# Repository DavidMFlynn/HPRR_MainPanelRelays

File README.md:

# HPRR_MainPanelRelays
 Block Power Relays

Aux Relays:
2x 4PDT relays with diodes and connectors.

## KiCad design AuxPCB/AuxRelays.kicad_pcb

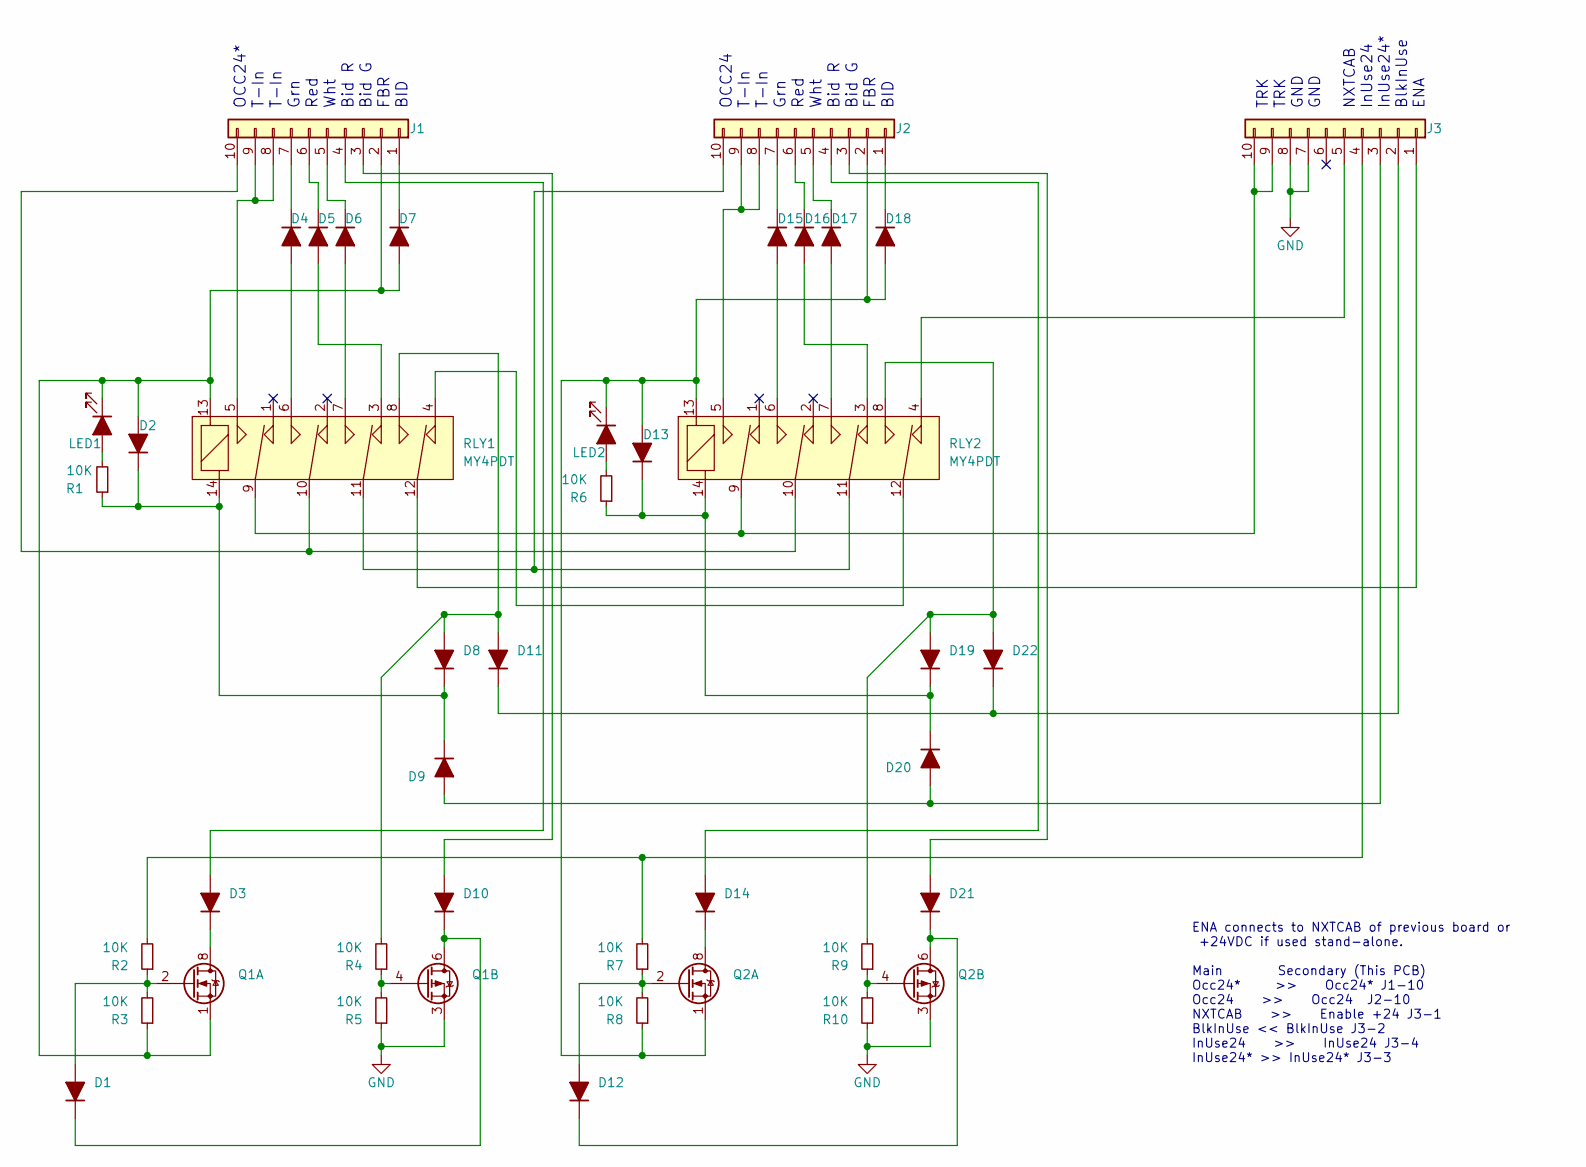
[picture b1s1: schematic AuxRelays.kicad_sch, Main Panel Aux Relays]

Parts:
D1, D2, D3, D4, D5, D6, D7, D8, D9, D10, D11, D12, D13, D14, D15, D16, D17, D18, D19, D20, D21, D22: SMA; D_SMA
J1, J2, J3: Conn_01x10; TerminalBlock_Phoenix_PT-1,5-10-3.5-H_1x10_P3.50mm_Horizont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
LED1, LED2: LED; LED_1206_3216Metric_Pad1.42x1.75mm_HandSolder
Q1, Q2: IRF7343PBF; SOIC-8_3.9x4.9mm_P1.27mm
R1, R2, R3, R4, R5, R6, R7, R8, R9, R10: 10K; R_0805_2012Metric_Pad1.20x1.40mm_HandSolder
RLY1, RLY2: MY4PDT

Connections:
GND: J3.7, J3.8, Q1.3 (1), Q2.3 (1), R5.1, R10.1
unnamed: D1.1 (K), D10.1 (K), Q1.5 (D), Q1.6 (D)
unnamed: D1.2 (A), Q1.2 (G), R2.1, R3.2
unnamed: D2.1 (K), D8.1 (K), D9.1 (K), R1.1, RLY1.14
unnamed: D2.2 (A), D7.2 (A), J1.2, LED1.1 (K), Q1.1 (S), R3.1, RLY1.13
unnamed: D3.1 (K), Q1.7 (D), Q1.8 (D)
unnamed: D3.2 (A), J1.4
unnamed: D4.1 (K), J1.7
unnamed: D4.2 (A), RLY1.6
unnamed: D5.1 (K), J1.6
unnamed: D5.2 (A), RLY1.3
unnamed: D6.1 (K), J1.5
unnamed: D6.2 (A), RLY1.7
unnamed: D7.1 (K), J1.1
unnamed: D10.2 (A), J1.3
unnamed: D11.1 (K), D22.1 (K), J3.2
unnamed: D8.2 (A), D11.2 (A), R4.2, RLY1.8
unnamed: D12.1 (K), D21.1 (K), Q2.5 (D), Q2.6 (D)
unnamed: D12.2 (A), Q2.2 (G), R7.1, R8.2
unnamed: D13.1 (K), D19.1 (K), D20.1 (K), R6.1, RLY2.14
unnamed: D13.2 (A), D18.2 (A), J2.2, LED2.1 (K), Q2.1 (S), R8.1, RLY2.13
unnamed: D14.1 (K), Q2.7 (D), Q2.8 (D)
unnamed: D14.2 (A), J2.4
unnamed: D15.1 (K), J2.7
unnamed: D15.2 (A), RLY2.6
unnamed: D16.1 (K), J2.6
unnamed: D16.2 (A), RLY2.3
unnamed: D17.1 (K), J2.5
unnamed: D17.2 (A), RLY2.7
unnamed: D18.1 (K), J2.1
unnamed: D19.2 (A), D22.2 (A), R9.2, RLY2.8
unnamed: D9.2 (A), D20.2 (A), J3.3
unnamed: D21.2 (A), J2.3
unnamed: J1.8, J1.9, RLY1.5
unnamed: J1.10, RLY1.10, RLY2.10
unnamed: J2.8, J2.9, RLY2.5
unnamed: J2.10, RLY1.11, RLY2.11
unnamed: J3.1, RLY1.12
unnamed: J3.4, R2.2, R7.2
unnamed: J3.5, RLY2.4
unnamed: J3.9, J3.10, RLY1.9, RLY2.9
unnamed: LED1.2 (A), R1.2
unnamed: LED2.2 (A), R6.2
unnamed: Q1.4 (G), R4.1, R5.2
unnamed: Q2.4 (G), R9.1, R10.2
unnamed: RLY1.4, RLY2.12

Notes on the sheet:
OCC24* T-In T-In Grn Red Wht Bid R Bid G FBR BID
OCC24 T-In T-In Grn Red Wht Bid R Bid G FBR BID
ENA connects to NXTCAB of previous board or +24VDC if used stand-alone. Main Secondary (This PCB) Occ24* >> Occ24* J1-10 Occ24 >> Occ24 J2-10 NXTCAB >> Enable +24 J3-1 BlkInUse << BlkInUse J3-2 InUse24 >> InUse24 J3-4 InUse24* >> InUse24* J3-3
TRK TRK GND GND NXTCAB InUse24 InUse24* BlkInUse ENA

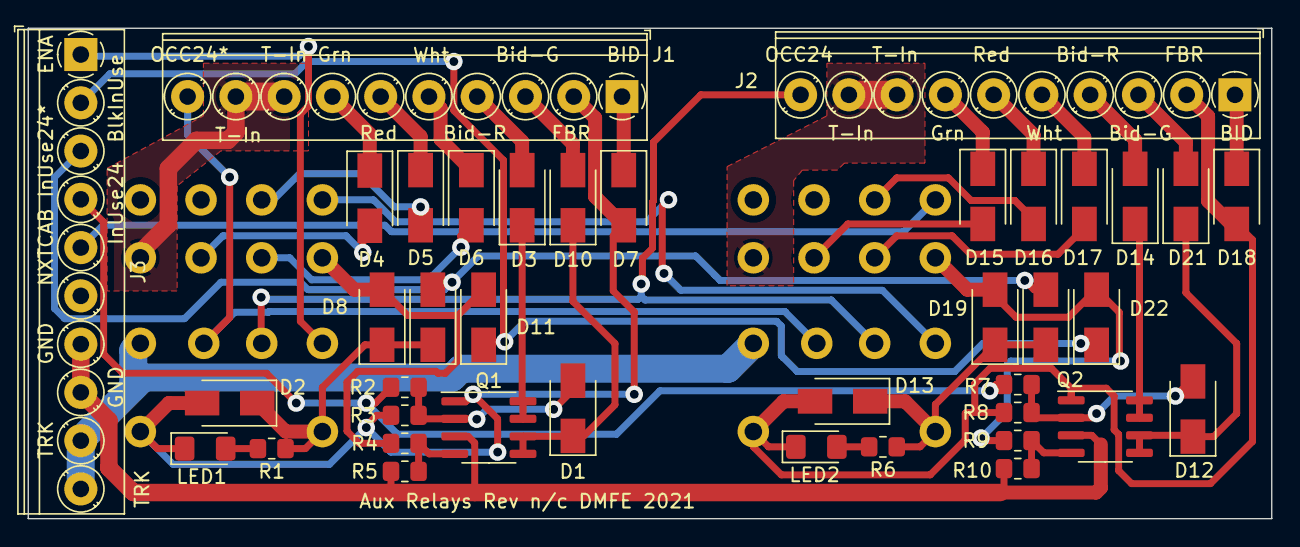
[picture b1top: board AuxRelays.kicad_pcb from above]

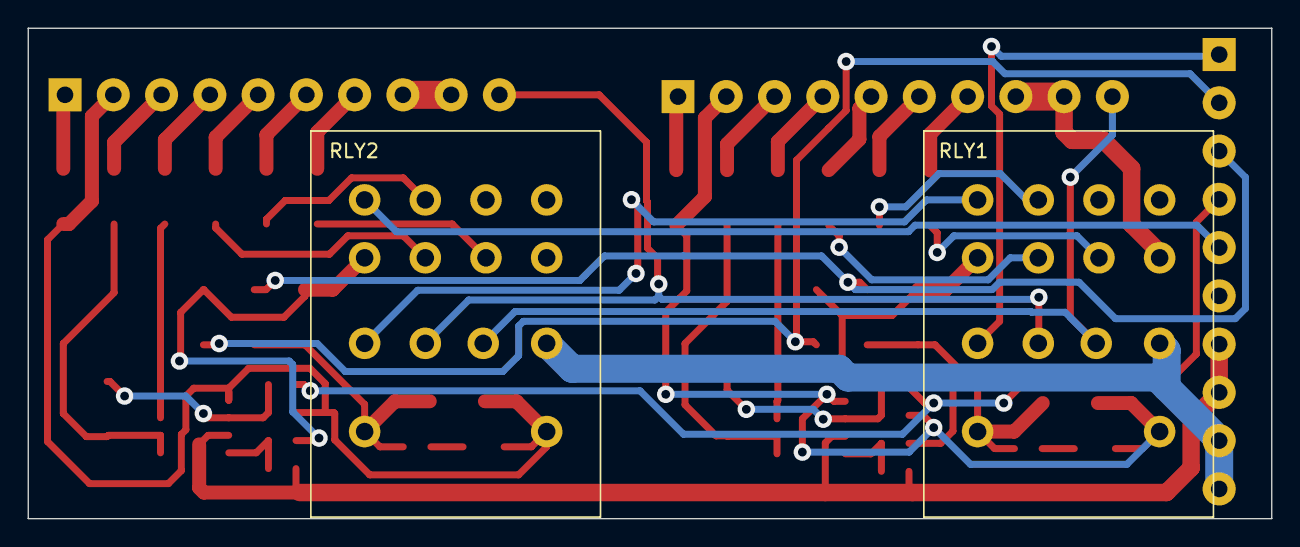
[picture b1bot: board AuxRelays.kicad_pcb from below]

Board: 2 copper layers, 90.2 x 35.6 mm, 41 parts (2 on the bottom side), 46 nets.

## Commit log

2021-02-26 Started schematic
2021-02-26 Added old schematic
2021-02-27 update of kicad
2021-02-27 Done and OSHPARKed
